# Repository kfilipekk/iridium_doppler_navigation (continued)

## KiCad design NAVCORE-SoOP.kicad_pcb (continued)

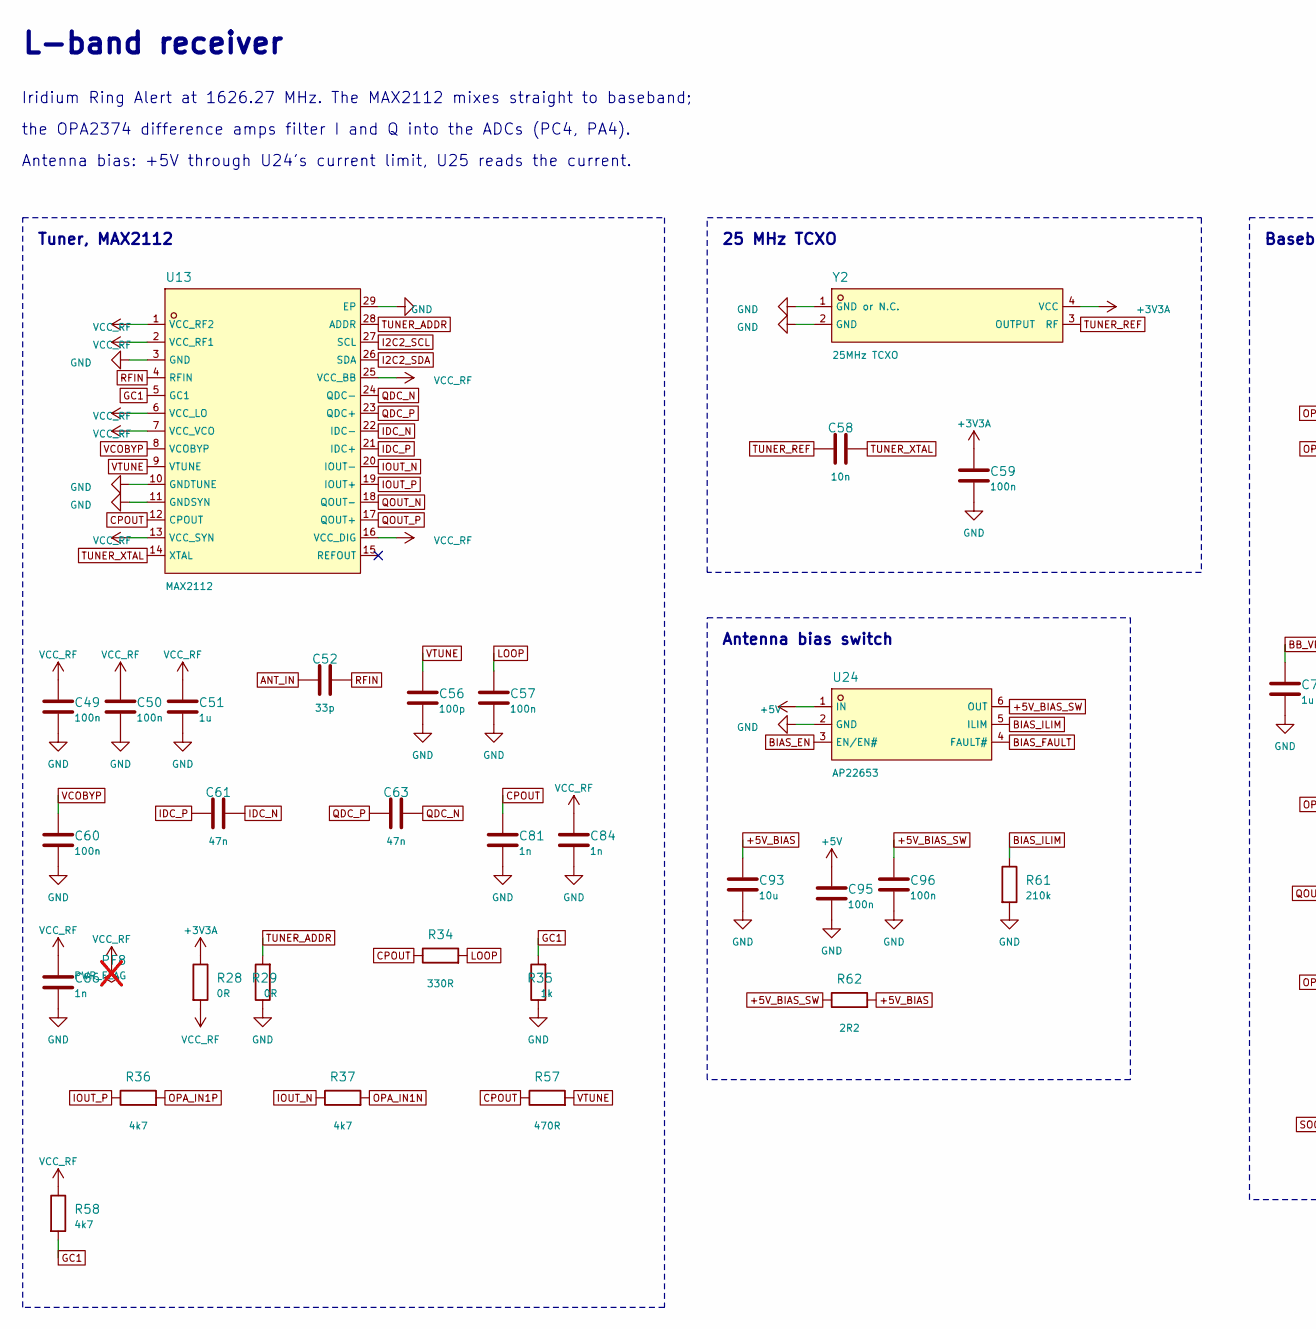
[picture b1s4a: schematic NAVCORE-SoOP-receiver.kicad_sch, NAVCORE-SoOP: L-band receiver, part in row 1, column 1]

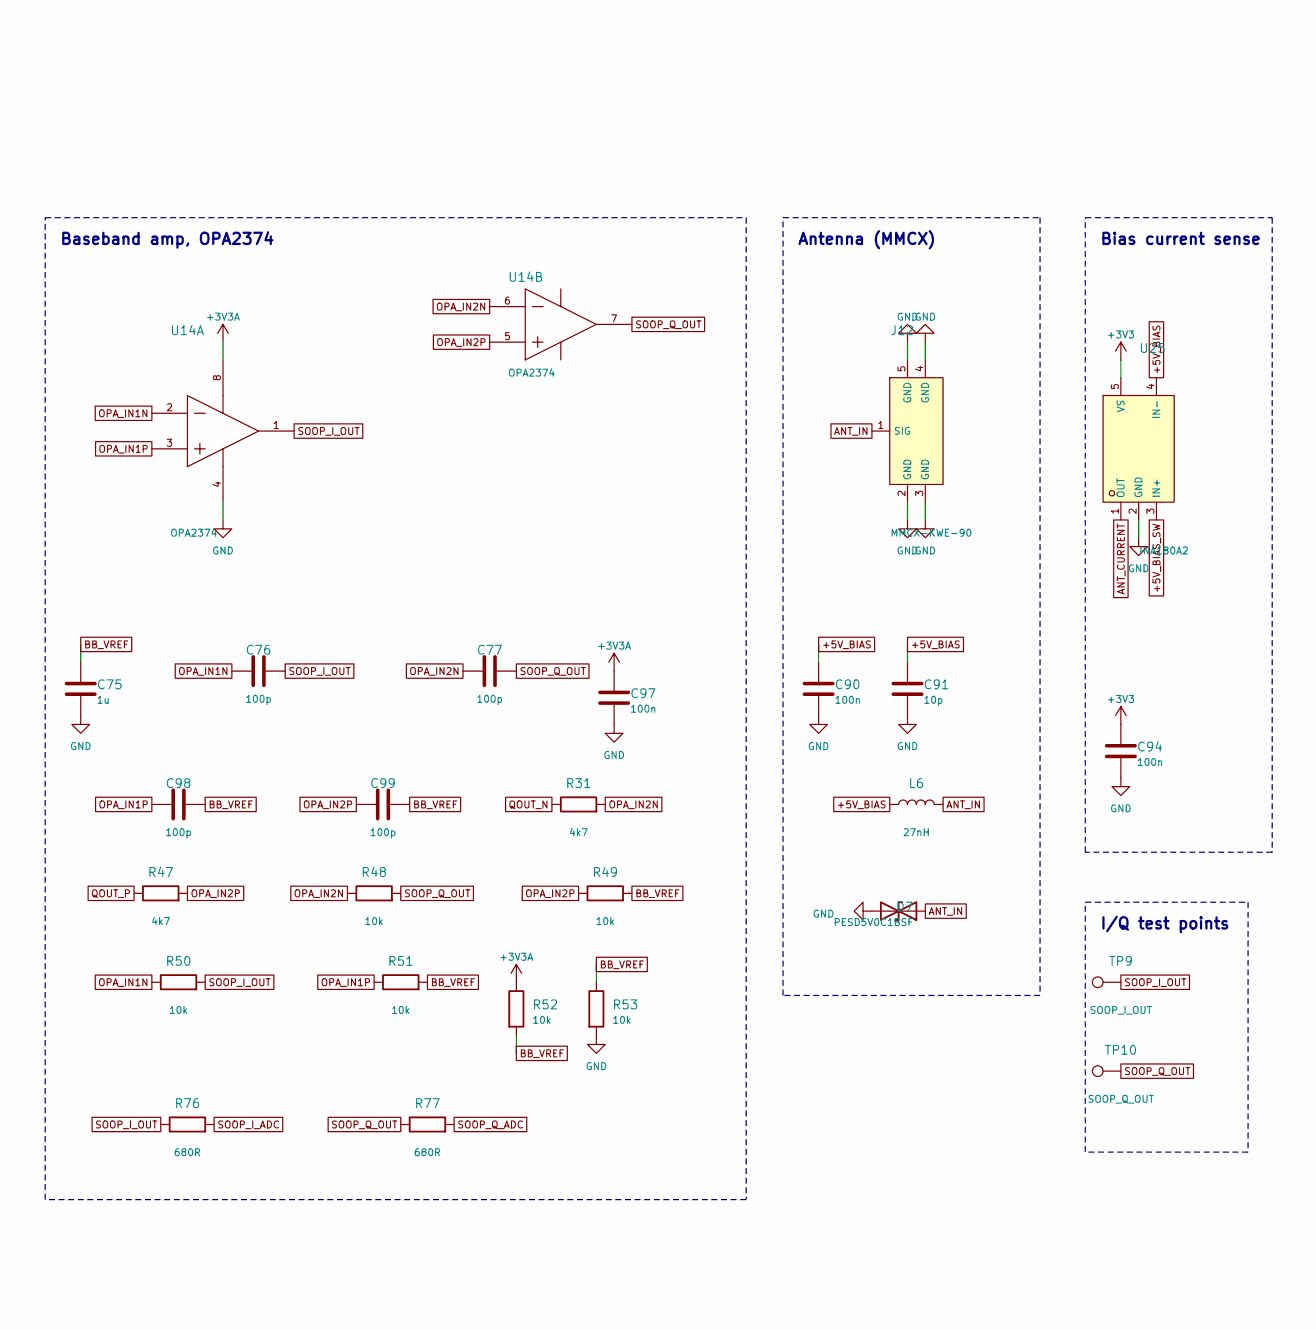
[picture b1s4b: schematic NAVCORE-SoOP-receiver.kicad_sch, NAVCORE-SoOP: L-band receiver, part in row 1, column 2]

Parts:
C49, C50, C57, C60, C90, C94, C95, C96: 100n; C_0402_1005Metric; LCSC C1525
C51, C75: 1u; C_0402_1005Metric; LCSC C52923
C52: 33p; C_0402_1005Metric; LCSC C1562
C56, C98, C99: 100p; C_0201_0603Metric; LCSC C62550
C58: 10n; C_0402_1005Metric; LCSC C15195
C59, C97: 100n; C_0201_0603Metric; LCSC C76939
C61, C63: 47n; C_0402_1005Metric; LCSC C82219
C76, C77: 100p; C_0402_1005Metric; LCSC C1546
C81, C84, C86: 1n; C_0402_1005Metric; LCSC C1523
C91: 10p; C_0402_1005Metric; LCSC C32949
C93: 10u; C_0805_2012Metric; LCSC C15850
D7: PESD5V0C1BSF; DSN0603-2_L0.6-W0.3-P0.40-BI; LCSC C477955
J12: MMCX-KWE-90; MMCX-TH_DL-MMCX-KWE-90; LCSC C2894793
L6: 27nH; L0402; LCSC C113111
PF8: PWR_FLAG; not fitted
R28, R29: 0R; R_0402_1005Metric; LCSC C17168
R31, R36, R37, R47, R58: 4k7; R_0402_1005Metric; LCSC C25900
R34: 330R; R_0402_1005Metric; LCSC C25104
R35: 1k; R_0402_1005Metric; LCSC C11702
R48, R49, R50, R51, R52, R53: 10k; R_0402_1005Metric; LCSC C25744
R57: 470R; R_0402_1005Metric; LCSC C25117
R61: 210k; R_0402_1005Metric; LCSC C58827
R62: 2R2; R_0402_1005Metric; LCSC C1881139
R76, R77: 680R; R_0201_0603Metric; LCSC C473509
TP9: SOOP_I_OUT; TestPoint_Pad_1.5x1.5mm
TP10: SOOP_Q_OUT; TestPoint_Pad_1.5x1.5mm
U13: MAX2112; TQFN-28_L5.0-W5.0-P0.50-BL-EP3.3; LCSC C596391
U14: OPA2374; SOP-8_L4.9-W3.9-P1.27-LS6.0-BL; LCSC C444392
U24: AP22653; SOT-23-6_L2.9-W1.6-P0.95-LS2.8-BR; LCSC C2158037
U25: INA180A2; SOT-23-5_L3.0-W1.7-P0.95-LS2.8-BL; LCSC C192764
Y2: 25MHz TCXO; OSC-SMD_4P-L3.2-W2.5-BL; LCSC C19674258

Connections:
+3V3: C94.1, U25.5 (VS); also elsewhere on the board
+3V3A: C59.1, C97.1, R28.1, R52.1, U14.8 (VCC+), Y2.4 (VCC); also elsewhere on the board
+5V: C95.1, U24.1 (IN); also elsewhere on the board
+5V_BIAS: C90.1, C91.1, C93.1, L6.1, R62.2, U25.4 (IN-)
+5V_BIAS_SW: C96.1, R62.1, U24.6 (OUT), U25.3 (IN+)
ANT_CURRENT: U25.1 (OUT); also elsewhere on the board
ANT_IN: C52.1, D7.1 (A1), J12.1 (SIG), L6.2
BB_VREF: C75.1, C98.2, C99.2, R49.2, R51.2, R52.2, R53.1
BIAS_EN: U24.3 (EN/EN#); also elsewhere on the board
BIAS_FAULT: U24.4 (FAULT#); also elsewhere on the board
BIAS_ILIM: R61.1, U24.5 (ILIM)
CPOUT: C81.1, R34.1, R57.1, U13.12 (CPOUT)
GC1: R35.2, R58.2, U13.5 (GC1)
GND: C49.2, C50.2, C51.2, C56.2, C57.2, C59.2, C60.2, C75.2, C81.2, C84.2, C86.2, C90.2, C91.2, C93.2, C94.2, C95.2, C96.2, C97.2, D7.2 (A2), J12.2 (GND), J12.3 (GND), J12.4 (GND), J12.5 (GND), R29.1, R35.1, R53.2, R61.2, U13.3 (GND), U13.10 (GNDTUNE), U13.11 (GNDSYN), U13.29 (EP), U14.4 (VCC-), U24.2 (GND), U25.2 (GND), Y2.1 (GND or N.C.), Y2.2 (GND); also elsewhere on the board
I2C2_SCL: U13.27 (SCL); also elsewhere on the board
I2C2_SDA: U13.26 (SDA); also elsewhere on the board
IDC_N: C61.2, U13.22 (IDC-)
IDC_P: C61.1, U13.21 (IDC+)
IOUT_N: R37.1, U13.20 (IOUT-)
IOUT_P: R36.1, U13.19 (IOUT+)
LOOP: C57.1, R34.2
OPA_IN1N: C76.1, R37.2, R50.1, U14.2 (IN1-)
OPA_IN1P: C98.1, R36.2, R51.1, U14.3 (IN1+)
OPA_IN2N: C77.1, R31.2, R48.1, U14.6 (IN2-)
OPA_IN2P: C99.1, R47.2, R49.1, U14.5 (IN2+)
QDC_N: C63.2, U13.24 (QDC-)
QDC_P: C63.1, U13.23 (QDC+)
QOUT_N: R31.1, U13.18 (QOUT-)
QOUT_P: R47.1, U13.17 (QOUT+)
RFIN: C52.2, U13.4 (RFIN)
SOOP_I_ADC: R76.2; also elsewhere on the board
SOOP_I_OUT: C76.2, R50.2, R76.1, TP9.1, U14.1 (OUT1)
SOOP_Q_ADC: R77.2; also elsewhere on the board
SOOP_Q_OUT: C77.2, R48.2, R77.1, TP10.1, U14.7 (OUT2)
TUNER_ADDR: R29.2, U13.28 (ADDR)
TUNER_REF: C58.1, Y2.3 (OUTPUT RF)
TUNER_XTAL: C58.2, U13.14 (XTAL)
VCC_RF: C49.1, C50.1, C51.1, C84.1, C86.1, PF8.1, R28.2, R58.1, U13.1 (VCC_RF2), U13.2 (VCC_RF1), U13.6 (VCC_LO), U13.7 (VCC_VCO), U13.13 (VCC_SYN), U13.16 (VCC_DIG), U13.25 (VCC_BB)
VCOBYP: C60.1, U13.8 (VCOBYP)
VTUNE: C56.1, R57.2, U13.9 (VTUNE)

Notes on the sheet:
L-band receiver
Iridium Ring Alert at 1626.27 MHz. The MAX2112 mixes straight to baseband;
the OPA2374 difference amps filter I and Q into the ADCs (PC4, PA4).
Antenna bias: +5V through U24's current limit, U25 reads the current.
Tuner, MAX2112
25 MHz TCXO
Baseband amp, OPA2374
Antenna (MMCX)
Antenna bias switch
Bias current sense
I/Q test points

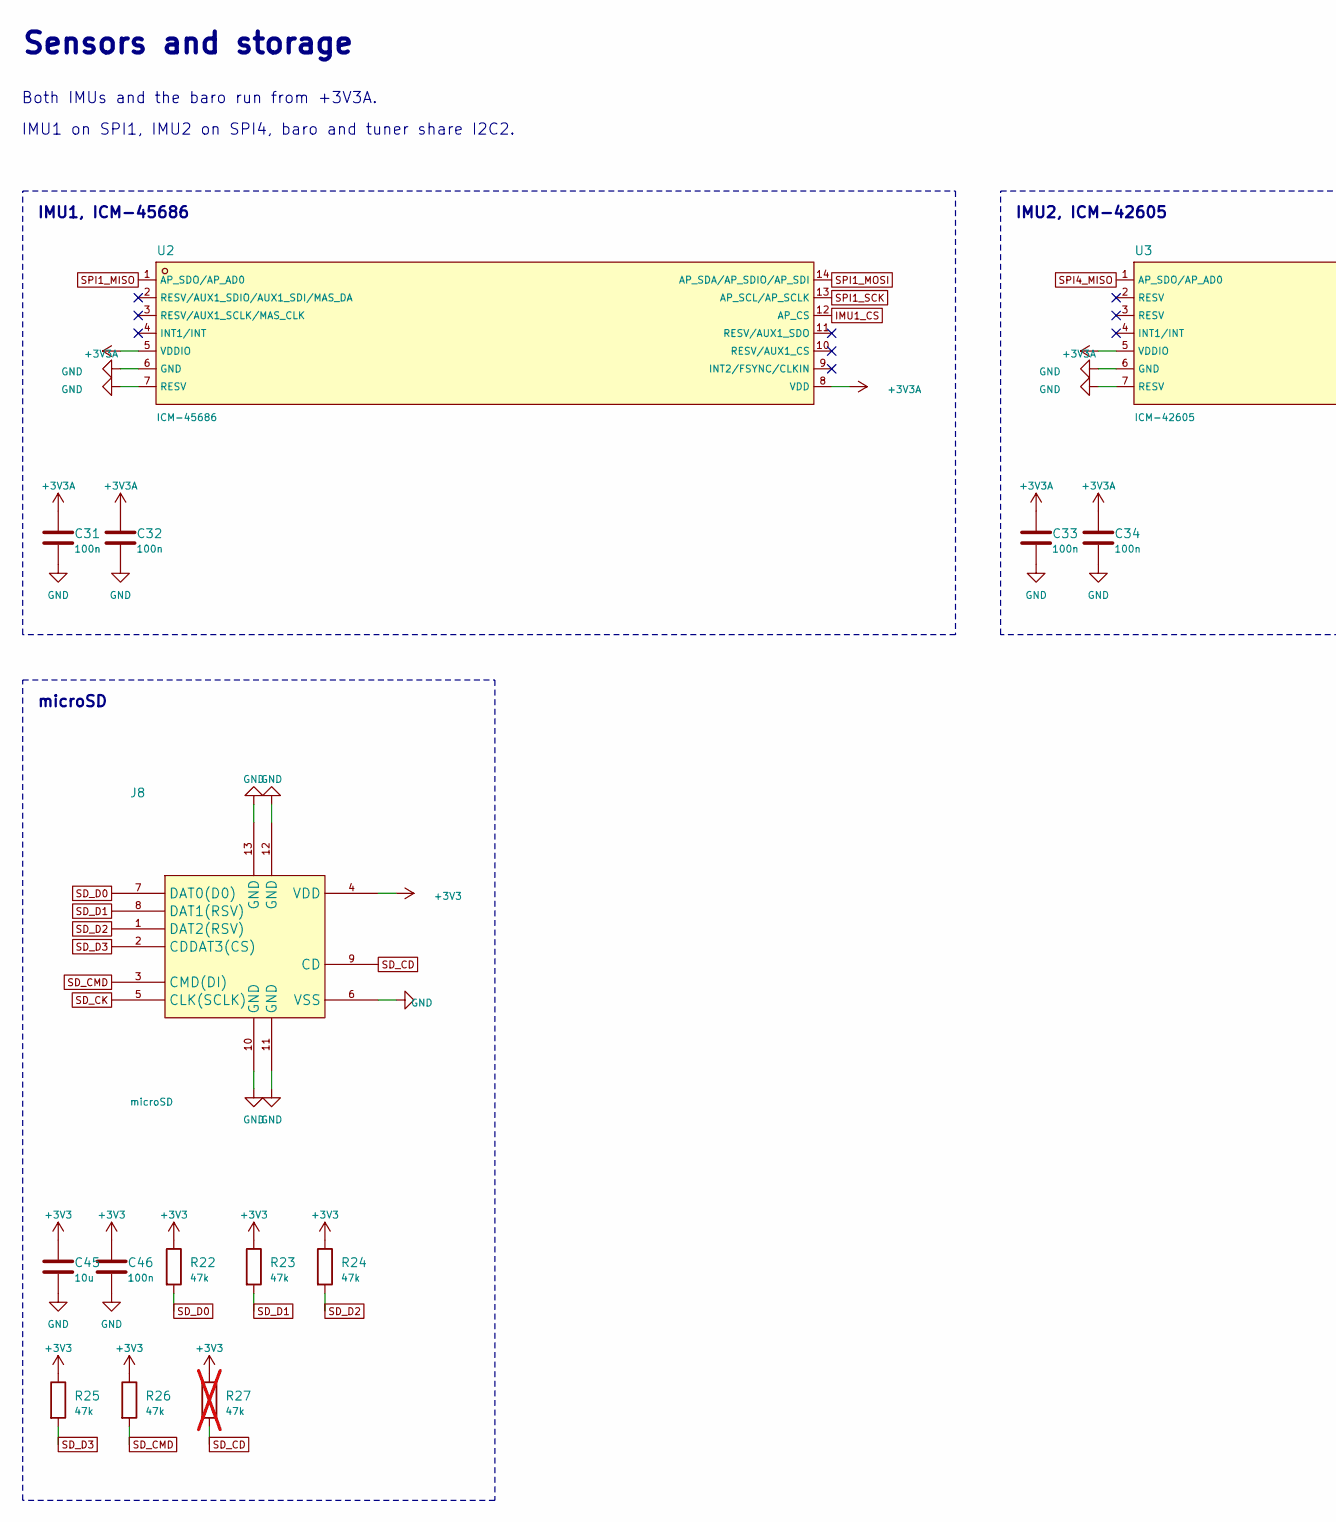
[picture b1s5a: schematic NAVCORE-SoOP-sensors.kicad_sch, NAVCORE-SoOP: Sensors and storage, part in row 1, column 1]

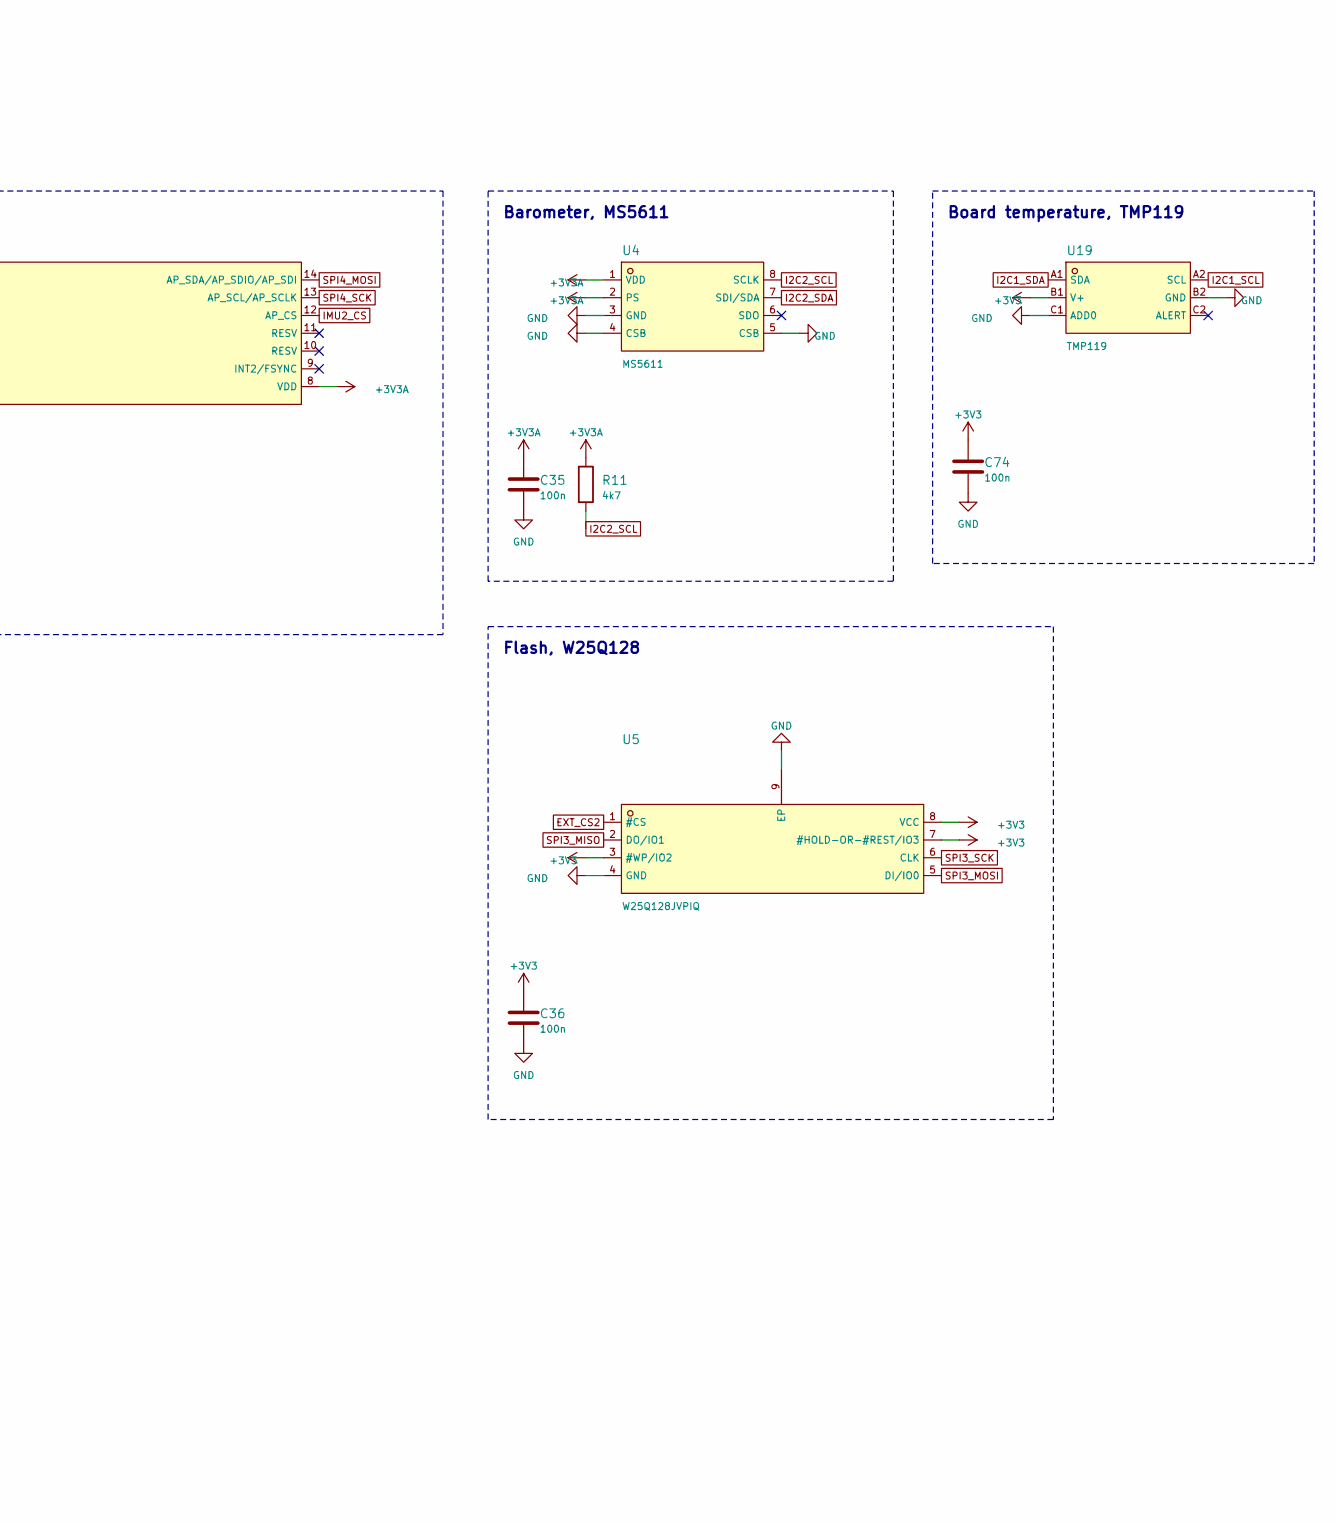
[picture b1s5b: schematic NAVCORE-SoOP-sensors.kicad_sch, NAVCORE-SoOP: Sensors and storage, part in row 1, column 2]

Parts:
C31, C32, C33, C34, C35, C36, C46, C74: 100n; C_0402_1005Metric; LCSC C1525
C45: 10u; C_0805_2012Metric; LCSC C15850
J8: microSD; TF-SMD_TF-01A; LCSC C91145
R11: 4k7; R_0201_0603Metric; LCSC C270346
R22, R23, R24, R25, R26: 47k; R_0402_1005Metric; LCSC C25792
R27: 47k; R_0402_1005Metric; LCSC C25792; not fitted
U2: ICM-45686; LGA-14_L3.0-W2.5-P0.50-TL; LCSC C22459454
U3: ICM-42605; LGA-14_L3.0-W2.5-P0.50-TL; LCSC C2655099
U4: MS5611; SENSORS-SMD_MS5611-01BA03; LCSC C15639
U5: W25Q128JVPIQ; WSON-8-1EP_6x5mm_P1.27mm_EP3.4x4.3mm; LCSC C190862
U19: TMP119; DSBGA-6_L1.5-W1.0-R2-C3-P0.40-BL; LCSC C22428347

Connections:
+3V3: C36.1, C45.1, C46.1, C74.1, J8.4 (VDD), R22.1, R23.1, R24.1, R25.1, R26.1, R27.1, U5.3 (#WP/IO2), U5.7 (#HOLD-OR-#REST/IO3), U5.8 (VCC), U19.B1 (V+); also elsewhere on the board
+3V3A: C31.1, C32.1, C33.1, C34.1, C35.1, R11.1, U2.5 (VDDIO), U2.8 (VDD), U3.5 (VDDIO), U3.8 (VDD), U4.1 (VDD), U4.2 (PS); also elsewhere on the board
EXT_CS2: U5.1 (#CS); also elsewhere on the board
GND: C31.2, C32.2, C33.2, C34.2, C35.2, C36.2, C45.2, C46.2, C74.2, J8.6 (VSS), J8.10 (GND), J8.11 (GND), J8.12 (GND), J8.13 (GND), U2.6 (GND), U2.7 (RESV), U3.6 (GND), U3.7 (RESV), U4.3 (GND), U4.4 (CSB), U4.5 (CSB), U5.4 (GND), U5.9 (EP), U19.B2 (GND), U19.C1 (ADD0); also elsewhere on the board
I2C1_SCL: U19.A2 (SCL); also elsewhere on the board
I2C1_SDA: U19.A1 (SDA); also elsewhere on the board
I2C2_SCL: R11.2, U4.8 (SCLK); also elsewhere on the board
I2C2_SDA: U4.7 (SDI/SDA); also elsewhere on the board
IMU1_CS: U2.12 (AP_CS); also elsewhere on the board
IMU2_CS: U3.12 (AP_CS); also elsewhere on the board
SD_CD: J8.9 (CD), R27.2
SD_CK: J8.5 (CLK(SCLK)); also elsewhere on the board
SD_CMD: J8.3 (CMD(DI)), R26.2; also elsewhere on the board
SD_D0: J8.7 (DAT0(D0)), R22.2; also elsewhere on the board
SD_D1: J8.8 (DAT1(RSV)), R23.2; also elsewhere on the board
SD_D2: J8.1 (DAT2(RSV)), R24.2; also elsewhere on the board
SD_D3: J8.2 (CDDAT3(CS)), R25.2; also elsewhere on the board
SPI1_MISO: U2.1 (AP_SDO/AP_AD0); also elsewhere on the board
SPI1_MOSI: U2.14 (AP_SDA/AP_SDIO/AP_SDI); also elsewhere on the board
SPI1_SCK: U2.13 (AP_SCL/AP_SCLK); also elsewhere on the board
SPI3_MISO: U5.2 (DO/IO1); also elsewhere on the board
SPI3_MOSI: U5.5 (DI/IO0); also elsewhere on the board
SPI3_SCK: U5.6 (CLK); also elsewhere on the board
SPI4_MISO: U3.1 (AP_SDO/AP_AD0); also elsewhere on the board
SPI4_MOSI: U3.14 (AP_SDA/AP_SDIO/AP_SDI); also elsewhere on the board
SPI4_SCK: U3.13 (AP_SCL/AP_SCLK); also elsewhere on the board

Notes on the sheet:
Sensors and storage
Both IMUs and the baro run from +3V3A.
IMU1 on SPI1, IMU2 on SPI4, baro and tuner share I2C2.
IMU1, ICM-45686
IMU2, ICM-42605
Barometer, MS5611
Board temperature, TMP119
Flash, W25Q128
microSD

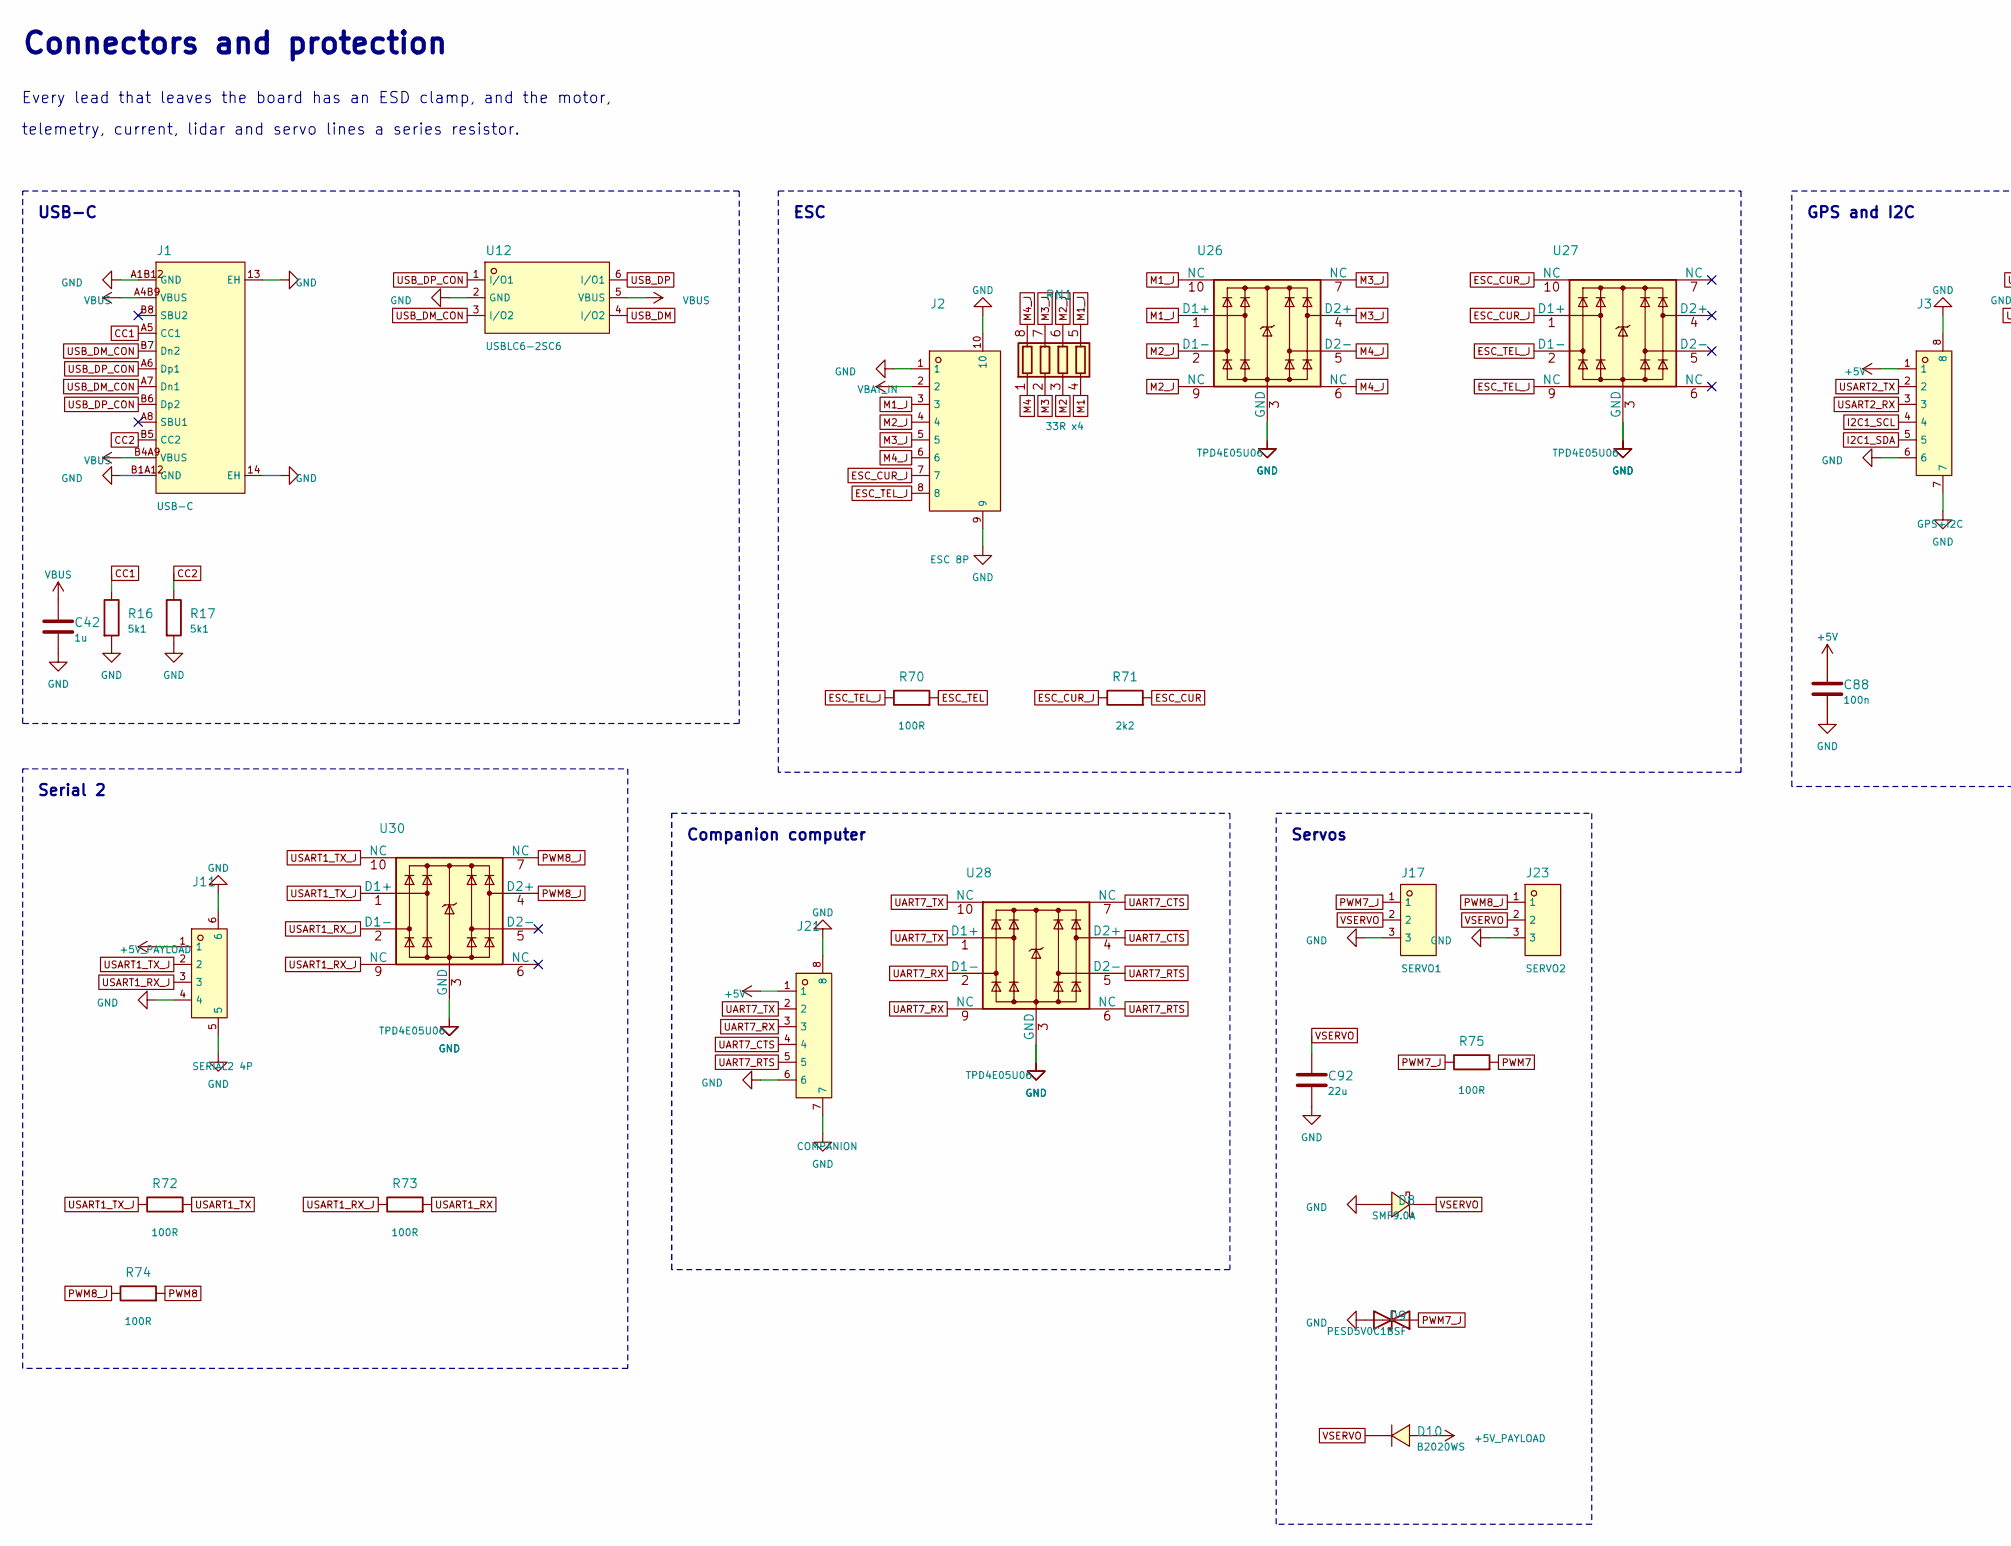
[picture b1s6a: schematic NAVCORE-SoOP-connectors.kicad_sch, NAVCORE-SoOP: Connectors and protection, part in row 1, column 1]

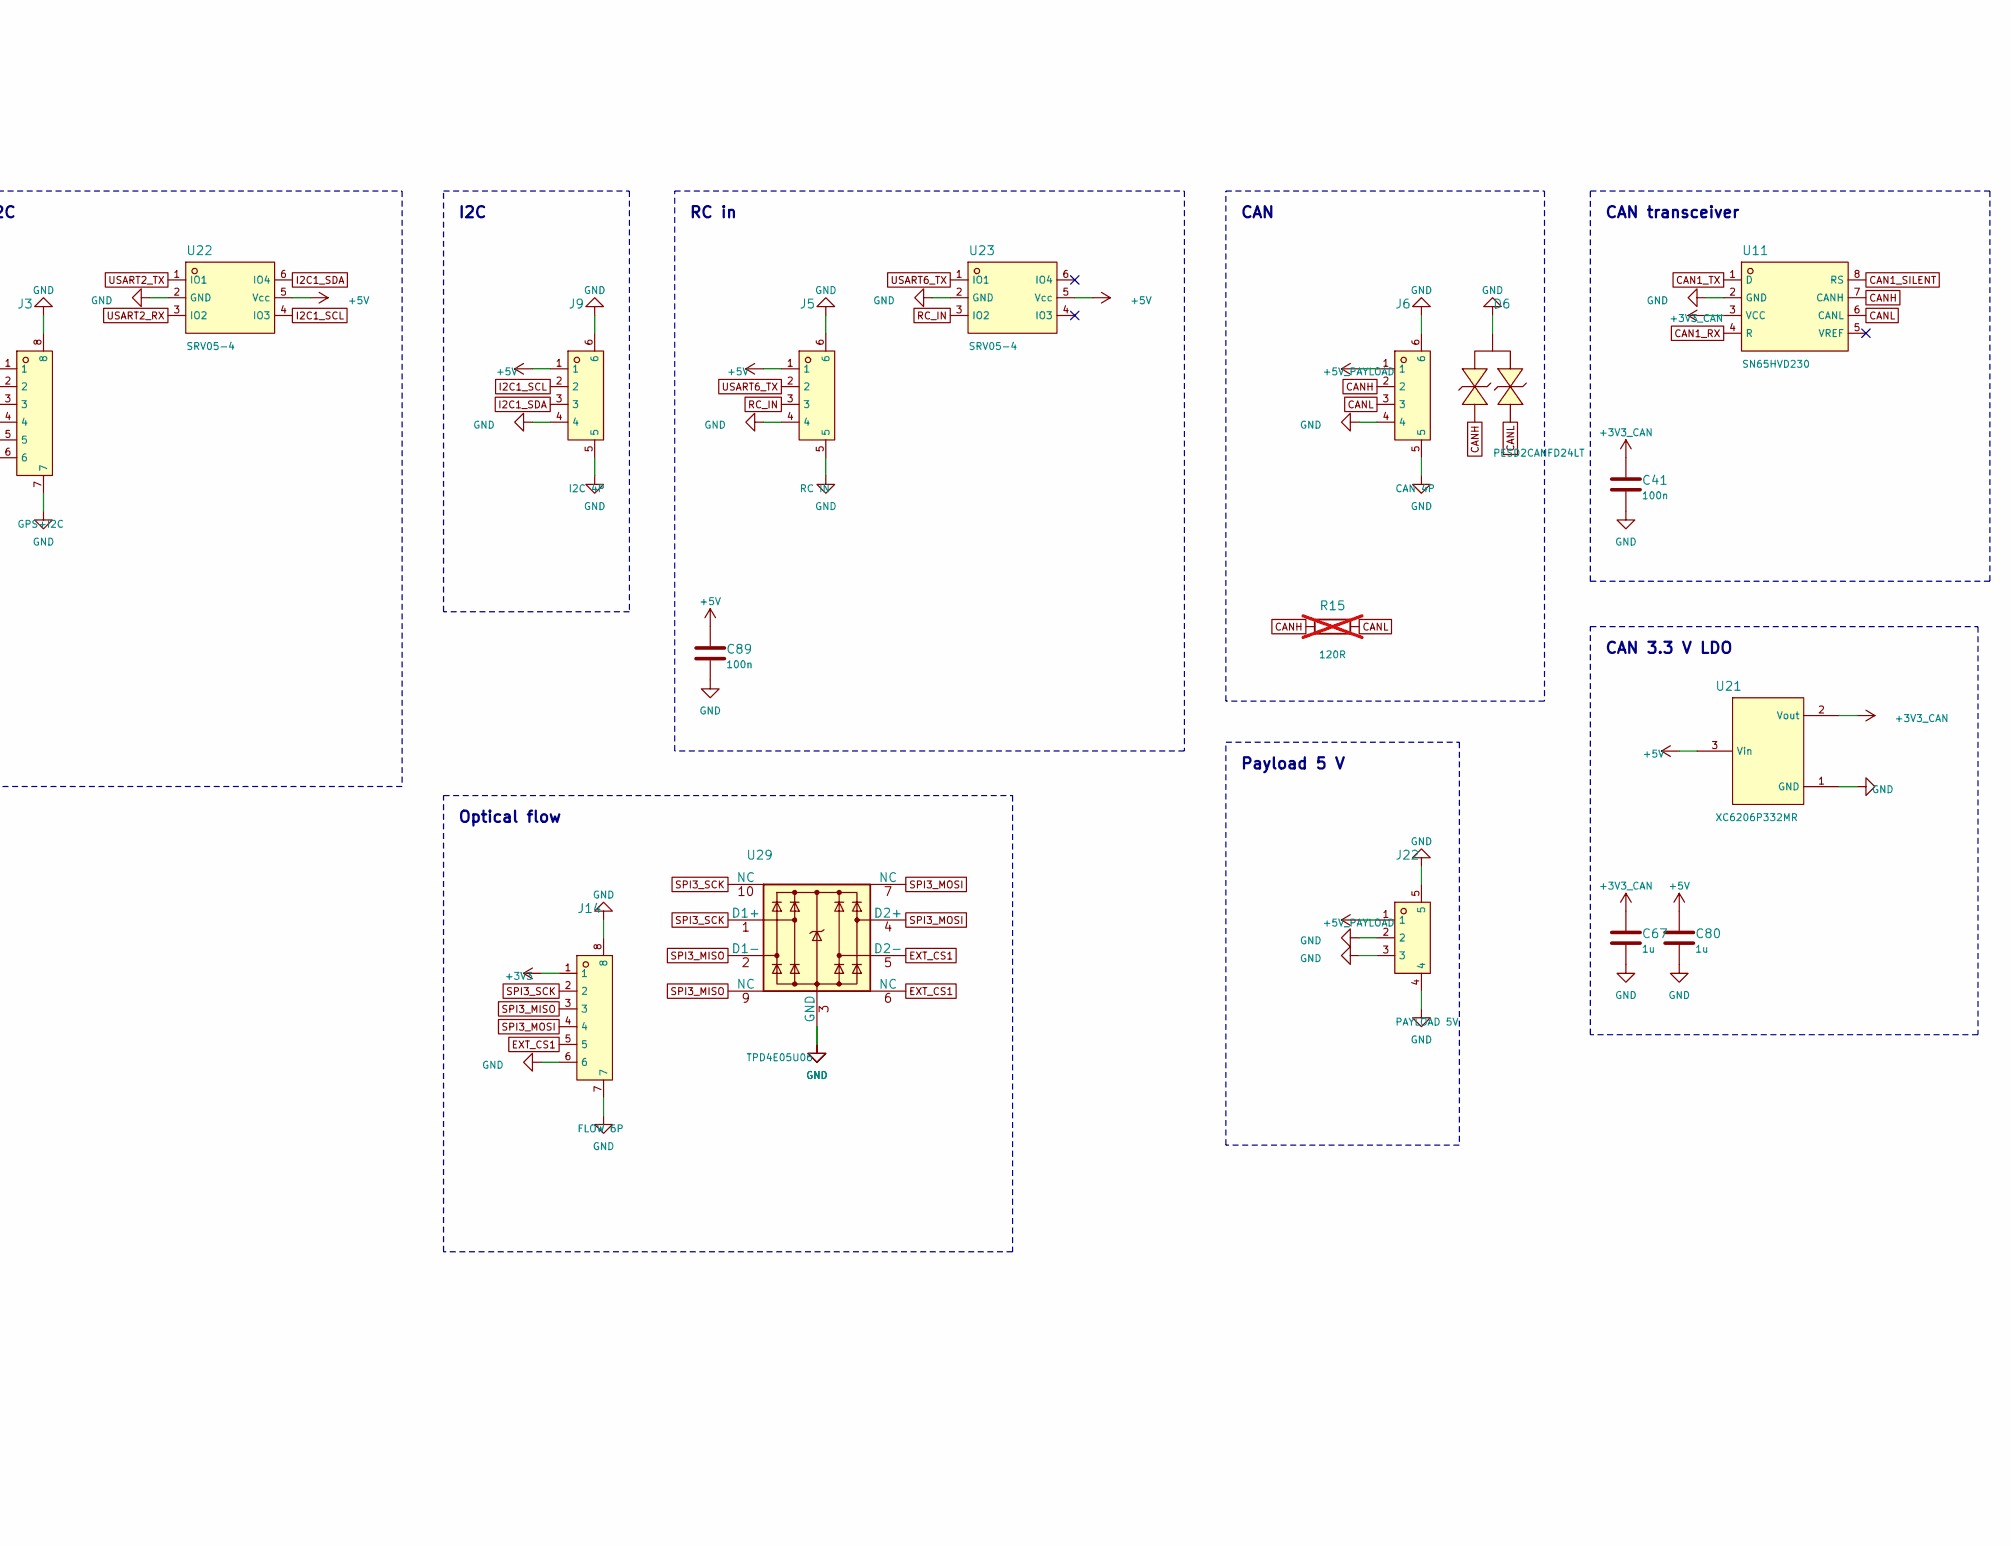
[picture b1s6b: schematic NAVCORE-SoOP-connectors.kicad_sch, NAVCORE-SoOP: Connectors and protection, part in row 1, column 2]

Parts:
C41, C88, C89: 100n; C_0402_1005Metric; LCSC C1525
C42: 1u; C_0805_2012Metric; LCSC C28323
C67, C80: 1u; C_0402_1005Metric; LCSC C52923
C92: 22u; C_1206_3216Metric; LCSC C12891
D6: PESD2CANFD24LT; SOT-23-3_L2.9-W1.6-P1.90-LS2.8-BR; LCSC C6952426
D8: SMF9.0A; SOD-123FL_L2.7-W1.8-LS3.7-RD; LCSC C1973343
D9: PESD5V0C1BSF; DSN0603-2_L0.6-W0.3-P0.40-BI; LCSC C477955
D10: B2020WS; SOD-323_L1.7-W1.3-LS2.7-RD; LCSC C77284
J1: USB-C; USB-C-SMD_TYPE-C-16PIN-2MD-073; LCSC C2765186
J2: ESC 8P; CONN-TH_SM08B-SRSS-TB-LF-SN; LCSC C160407
J3: GPS+I2C; CONN-SMD_XY-SM06B-GHS-TB; LCSC C51940119
J5: RC IN; CONN-SMD_4P-P1.25_BX-GH1.25-4PWT; LCSC C18077720
J6: CAN 4P; CONN-SMD_4P-P1.25_BX-GH1.25-4PWT; LCSC C18077720
J9: I2C 4P; CONN-SMD_4P-P1.25_BX-GH1.25-4PWT; LCSC C18077720
J11: SERIAL2 4P; CONN-SMD_4P-P1.25_BX-GH1.25-4PWT; LCSC C18077720
J14: FLOW 6P; CONN-SMD_XY-SM06B-GHS-TB; LCSC C51940119
J17: SERVO1; HDR-SMD_3P-P2.54-H-M_KH-2.54PH-1X3P-L13.5-WT; LCSC C20610212
J21: COMPANION; CONN-SMD_XY-SM06B-GHS-TB; LCSC C51940119
J22: PAYLOAD 5V; CONN-TH_SM03B-GHS-TB-LF-SN; LCSC C514175
J23: SERVO2; HDR-SMD_3P-P2.54-H-M_KH-2.54PH-1X3P-L13.5-WT; LCSC C20610212
R15: 120R; R_0402_1005Metric; LCSC C25079; not fitted
R16, R17: 5k1; R_0402_1005Metric; LCSC C25905
R70, R72, R73, R74, R75: 100R; R_0402_1005Metric; LCSC C25076
R71: 2k2; R_0402_1005Metric; LCSC C25879
RN1: 33R x4; R_Array_Convex_4x0402; LCSC C25501
U11: SN65HVD230; SOIC-8_L4.9-W3.9-P1.27-LS6.0-BL; LCSC C12084
U12: USBLC6-2SC6; SOT-23-6_L2.9-W1.6-P0.95-LS2.8-BL; LCSC C2687116
U21: XC6206P332MR; SOT-23-3_L2.9-W1.6-P1.90-LS2.8-BR; LCSC C5446
U22, U23: SRV05-4; SOT-23-6_L2.9-W1.6-P0.95-LS2.8-BR; LCSC C6454456
U26, U27, U28, U29, U30: TPD4E05U06; USON-10_2.5x1.0mm_P0.5mm; LCSC C138714

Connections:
+3V3: J14.1; also elsewhere on the board
+3V3_CAN: C41.1, C67.1, U11.3 (VCC), U21.2 (Vout)
+5V: C80.1, C88.1, C89.1, J3.1, J5.1, J9.1, J21.1, U21.3 (Vin), U22.5 (Vcc), U23.5 (Vcc); also elsewhere on the board
+5V_PAYLOAD: D10.2 (+), J6.1, J11.1, J22.1; also elsewhere on the board
CAN1_RX: U11.4 (R); also elsewhere on the board
CAN1_SILENT: U11.8 (RS); also elsewhere on the board
CAN1_TX: U11.1 (D); also elsewhere on the board
CANH: D6.1 (C), J6.2, R15.1, U11.7 (CANH)
CANL: D6.2 (C), J6.3, R15.2, U11.6 (CANL)
CC1: J1.A5 (CC1), R16.1
CC2: J1.B5 (CC2), R17.1
ESC_CUR: R71.2; also elsewhere on the board
ESC_CUR_J: J2.7, R71.1, U27.1 (D1+), U27.10 (NC)
ESC_TEL: R70.2; also elsewhere on the board
ESC_TEL_J: J2.8, R70.1, U27.2 (D1-), U27.9 (NC)
EXT_CS1: J14.5, U29.5 (D2-), U29.6 (NC); also elsewhere on the board
GND: C41.2, C42.2, C67.2, C80.2, C88.2, C89.2, C92.2, D6.3 (A), D8.2, D9.2 (A2), J1.13 (EH), J1.14 (EH), J1.A1B12 (GND), J1.B1A12 (GND), J2.1, J2.9, J2.10, J3.6, J3.7, J3.8, J5.4, J5.5, J5.6, J6.4, J6.5, J6.6, J9.4, J9.5, J9.6, J11.4, J11.5, J11.6, J14.6, J14.7, J14.8, J17.3, J21.6, J21.7, J21.8, J22.2, J22.3, J22.4, J22.5, J23.3, R16.2, R17.2, U11.2 (GND), U12.2 (GND), U21.1 (GND), U22.2 (GND), U23.2 (GND), U26.3 (GND), U26.8 (GND), U27.3 (GND), U27.8 (GND), U28.3 (GND), U28.8 (GND), U29.3 (GND), U29.8 (GND), U30.3 (GND), U30.8 (GND); also elsewhere on the board
I2C1_SCL: J3.4, J9.2, U22.4 (IO3); also elsewhere on the board
I2C1_SDA: J3.5, J9.3, U22.6 (IO4); also elsewhere on the board
M1: RN1.4 (R4.1); also elsewhere on the board
M1_J: J2.3, RN1.5 (R4.2), U26.1 (D1+), U26.10 (NC)
M2: RN1.3 (R3.1); also elsewhere on the board
M2_J: J2.4, RN1.6 (R3.2), U26.2 (D1-), U26.9 (NC)
M3: RN1.2 (R2.1); also elsewhere on the board
M3_J: J2.5, RN1.7 (R2.2), U26.4 (D2+), U26.7 (NC)
M4: RN1.1 (R1.1); also elsewhere on the board
M4_J: J2.6, RN1.8 (R1.2), U26.5 (D2-), U26.6 (NC)
PWM7: R75.2; also elsewhere on the board
PWM7_J: D9.1 (A1), J17.1, R75.1
PWM8: R74.2; also elsewhere on the board
PWM8_J: J23.1, R74.1, U30.4 (D2+), U30.7 (NC)
RC_IN: J5.3, U23.3 (IO2); also elsewhere on the board
SPI3_MISO: J14.3, U29.2 (D1-), U29.9 (NC); also elsewhere on the board
SPI3_MOSI: J14.4, U29.4 (D2+), U29.7 (NC); also elsewhere on the board
SPI3_SCK: J14.2, U29.1 (D1+), U29.10 (NC); also elsewhere on the board
UART7_CTS: J21.4, U28.4 (D2+), U28.7 (NC); also elsewhere on the board
UART7_RTS: J21.5, U28.5 (D2-), U28.6 (NC); also elsewhere on the board
UART7_RX: J21.3, U28.2 (D1-), U28.9 (NC); also elsewhere on the board
UART7_TX: J21.2, U28.1 (D1+), U28.10 (NC); also elsewhere on the board
USART1_RX: R73.2; also elsewhere on the board
USART1_RX_J: J11.3, R73.1, U30.2 (D1-), U30.9 (NC)
USART1_TX: R72.2; also elsewhere on the board
USART1_TX_J: J11.2, R72.1, U30.1 (D1+), U30.10 (NC)
USART2_RX: J3.3, U22.3 (IO2); also elsewhere on the board
USART2_TX: J3.2, U22.1 (IO1); also elsewhere on the board
USART6_TX: J5.2, U23.1 (IO1); also elsewhere on the board
USB_DM: U12.4 (I/O2); also elsewhere on the board
USB_DM_CON: J1.A7 (Dn1), J1.B7 (Dn2), U12.3 (I/O2)
USB_DP: U12.6 (I/O1); also elsewhere on the board
USB_DP_CON: J1.A6 (Dp1), J1.B6 (Dp2), U12.1 (I/O1)
VBAT_IN: J2.2; also elsewhere on the board
VBUS: C42.1, J1.A4B9 (VBUS), J1.B4A9 (VBUS), U12.5 (VBUS); also elsewhere on the board
VSERVO: C92.1, D8.1, D10.1 (-), J17.2, J23.2

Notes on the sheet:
Connectors and protection
Every lead that leaves the board has an ESD clamp, and the motor,
telemetry, current, lidar and servo lines a series resistor.
USB-C
ESC
GPS and I2C
I2C
RC in
CAN
CAN transceiver
CAN 3.3 V LDO
Serial 2
Optical flow
Companion computer
Payload 5 V
Servos

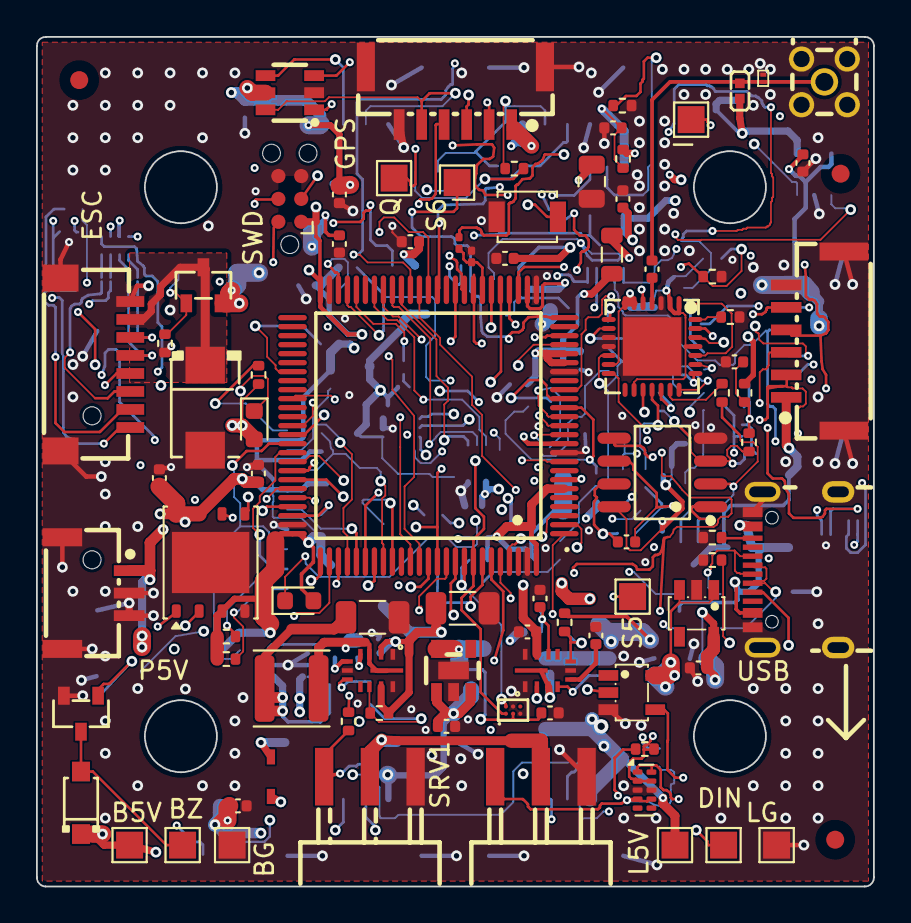
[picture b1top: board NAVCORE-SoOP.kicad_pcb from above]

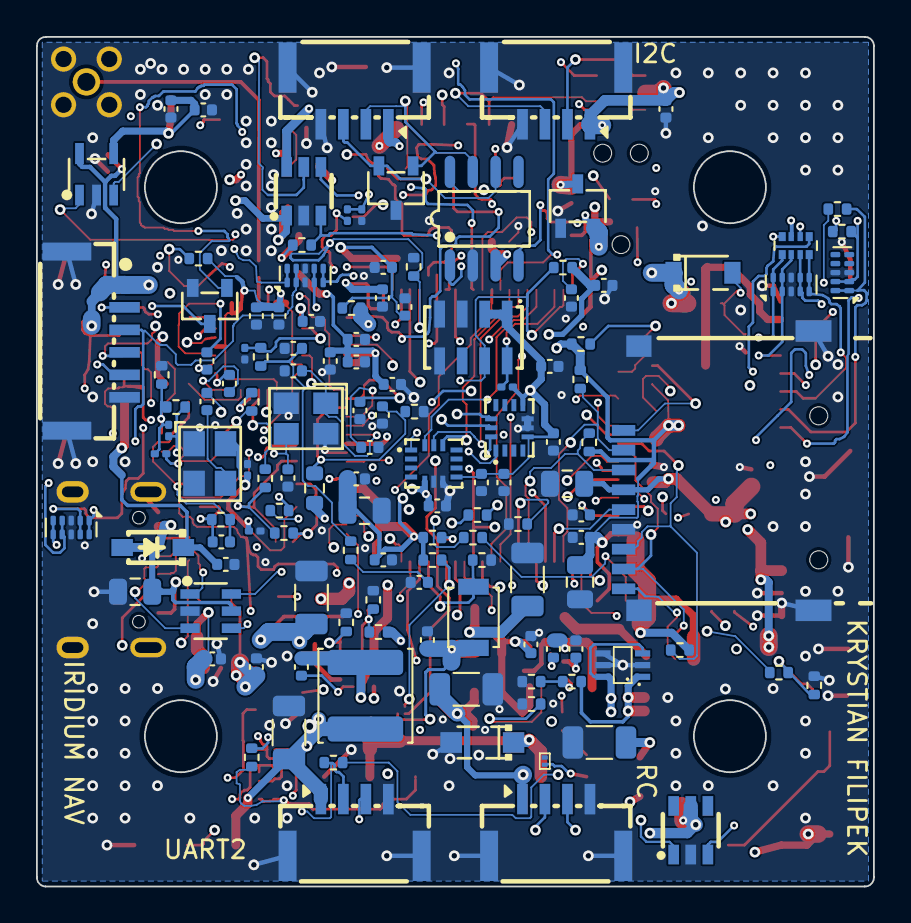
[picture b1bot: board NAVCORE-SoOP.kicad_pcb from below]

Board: 6 copper layers, 46.5 x 47.2 mm, 217 parts (129 on the bottom side), 141 nets.
